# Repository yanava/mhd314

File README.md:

# Mahaudio MHD314 Audio DAC for the RaspberryPi

This is a hardware project for an open Hi-Fi DAC design for the RaspberryPi. MHD stands for Mahaudio Hi-Fi DAC and 314 is an obvious reference to the Pi. 

## Description

This is a project conducted through a series of YouTube live events, which can be accessed on the following playlist: https://www.youtube.com/watch?v=isWnR_Fm9iQ&list=PLo5SrSJMaUGJOzglfgmpuGIEasF4YtCA1&pp=iAQB - Portuguese language only for now. The purpose is educational, to show audio enthusiasts what is the necessary work to develop and integrate a product.

## Presentations

All presentations used on the live events are available under the Documentation folder. 

## License

This project is licensed under the BSD-3 License.

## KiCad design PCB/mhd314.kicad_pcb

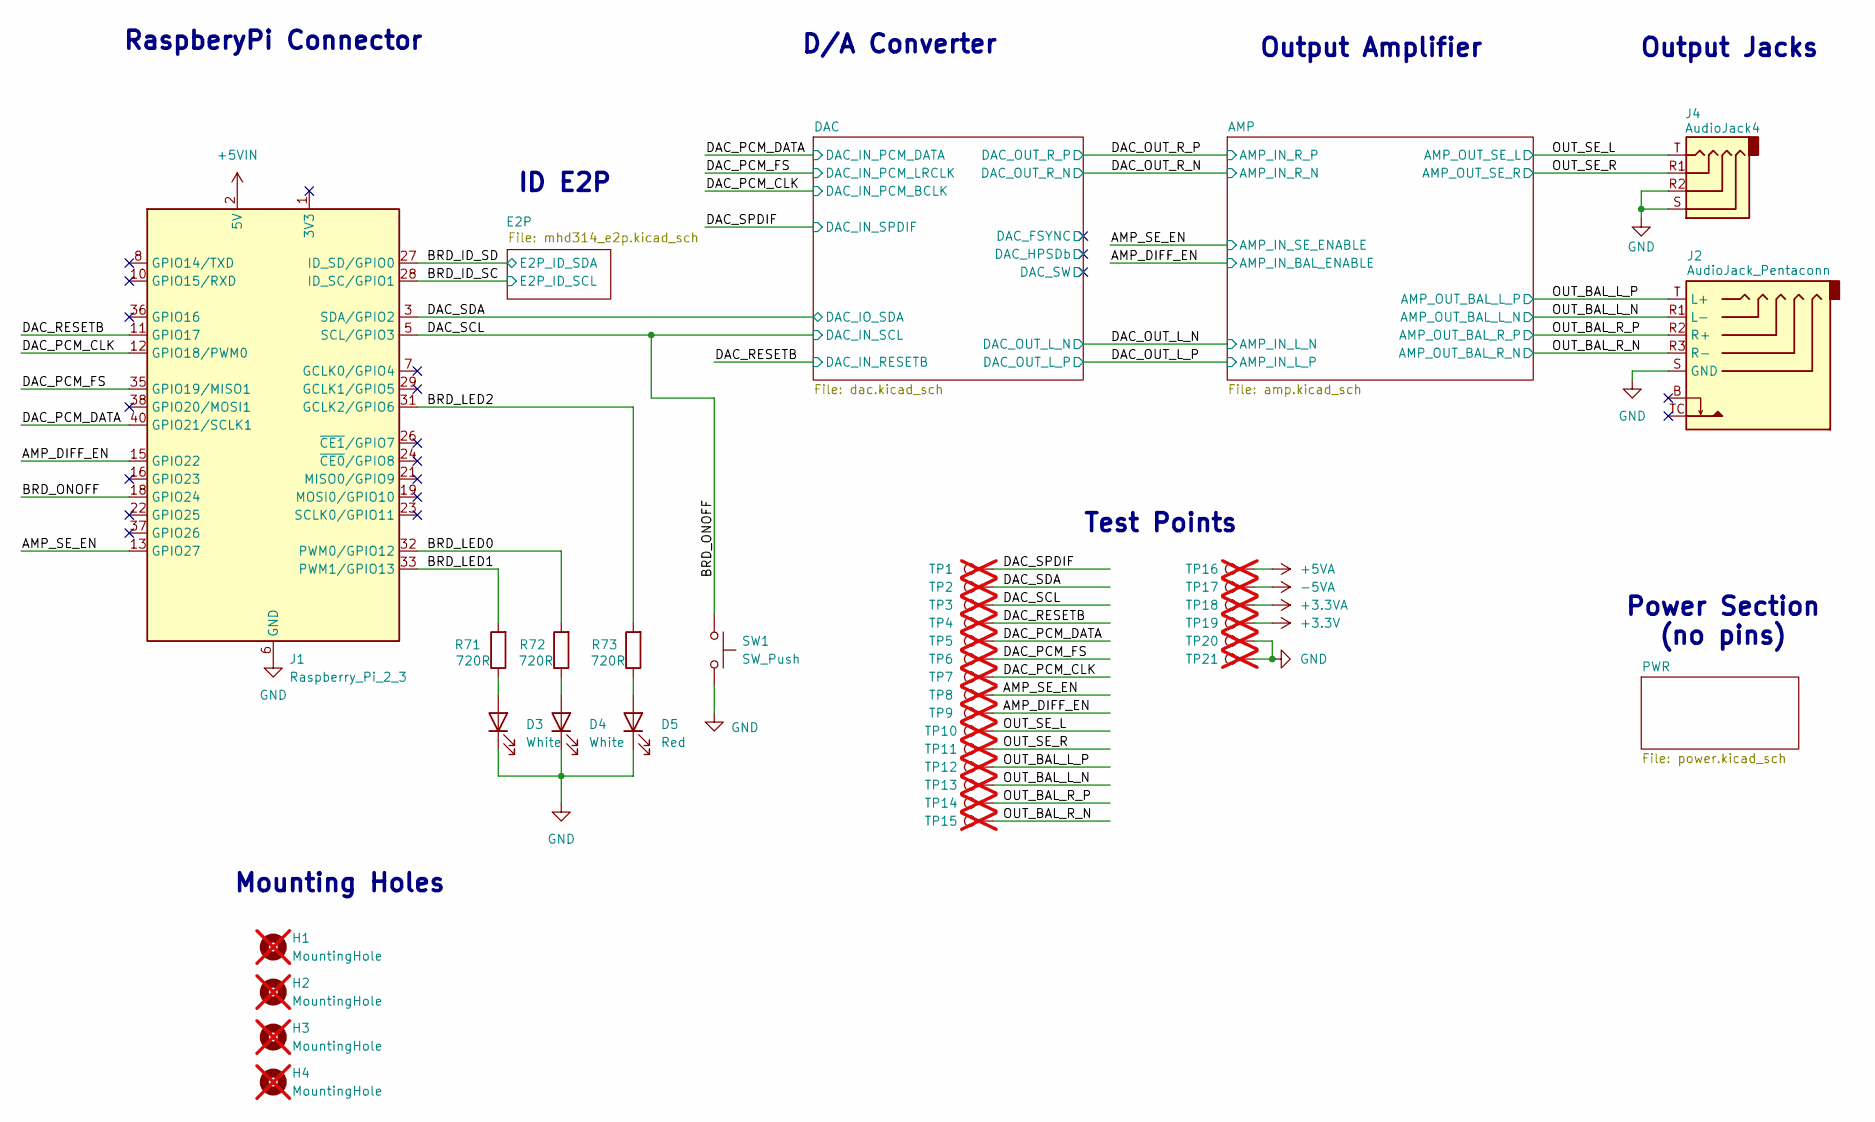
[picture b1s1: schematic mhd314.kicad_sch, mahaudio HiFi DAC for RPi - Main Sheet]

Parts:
D3, D4: White; LED_0603_1608Metric_Pad1.05x0.95mm_HandSolder; JLCPCB Part # C2290
D5: Red; LED_0603_1608Metric_Pad1.05x0.95mm_HandSolder; JLCPCB Part # C2286
H1, H2, H3, H4: MountingHole; MountingHole_2.7mm_M2.5_DIN965_Pad; not fitted
J1: Raspberry_Pi_2_3; PinSocket_2x20_P2.54mm_Vertical; JLCPCB Part # C132132
J2: AudioJack_Pentaconn; Jack_4.4mm_G-Switch_GT-3321667P-01_Horizontal; JLCPCB Part # C2762984
J4: AudioJack4; TENSILITY_54-00176; JLCPCB Part # C19857277
R71, R72, R73: 720R; R_0402_1005Metric_Pad0.72x0.64mm_HandSolder; Tolerance 1%; JLCPCB Part # C416571
SW1: SW_Push; SW_Tactile_SPST_Angled_PTS645Vx39-2LFS; JLCPCB Part # C285519
TP1, TP2, TP3, TP4, TP5, TP6, TP7, TP8, TP9, TP10, TP11, TP12, TP13, TP14, TP15, TP16, TP17, TP18, TP19, TP20, TP21: TestPoint; TestPoint_Pad_D1.0mm; not fitted

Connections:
+3.3V: TP19.1; also elsewhere on the board
+3.3VA: TP18.1; also elsewhere on the board
+5VA: TP16.1; also elsewhere on the board
+5VIN: J1.2 (5V), J1.4 (5V); also elsewhere on the board
-5VA: TP17.1; also elsewhere on the board
/AMP_DIFF_EN: J1.15 (GPIO22), TP9.1; also elsewhere on the board
/AMP_SE_EN: J1.13 (GPIO27), TP8.1; also elsewhere on the board
/BRD_ID_SC: J1.28 (ID_SC/GPIO1); also elsewhere on the board
/BRD_ID_SD: J1.27 (ID_SD/GPIO0); also elsewhere on the board
/BRD_LED0: J1.32 (PWM0/GPIO12), R72.2
/BRD_LED1: J1.33 (PWM1/GPIO13), R71.2
/BRD_LED2: J1.31 (GCLK2/GPIO6), R73.2
/BRD_ONOFF: J1.5 (SCL/GPIO3), J1.18 (GPIO24), SW1.1, TP3.1; also elsewhere on the board
/DAC_PCM_CLK: J1.12 (GPIO18/PWM0), TP7.1; also elsewhere on the board
/DAC_PCM_DATA: J1.40 (GPIO21/SCLK1), TP5.1; also elsewhere on the board
/DAC_PCM_FS: J1.35 (GPIO19/MISO1), TP6.1; also elsewhere on the board
/DAC_RESETB: J1.11 (GPIO17), TP4.1; also elsewhere on the board
/DAC_SDA: J1.3 (SDA/GPIO2), TP2.1; also elsewhere on the board
/DAC_SPDIF: TP1.1; also elsewhere on the board
/OUT_BAL_L_N: J2.R1 (L-), TP13.1; also elsewhere on the board
/OUT_BAL_L_P: J2.T (L+), TP12.1; also elsewhere on the board
/OUT_BAL_R_N: J2.R3 (R-), TP15.1; also elsewhere on the board
/OUT_BAL_R_P: J2.R2 (R+), TP14.1; also elsewhere on the board
/OUT_SE_L: J4.T, TP10.1; also elsewhere on the board
/OUT_SE_R: J4.R1, TP11.1; also elsewhere on the board
GND: D3.1 (K), D4.1 (K), D5.1 (K), J1.6 (GND), J1.9 (GND), J1.14 (GND), J1.20 (GND), J1.25 (GND), J1.30 (GND), J1.34 (GND), J1.39 (GND), J2.S (GND), J4.R2, J4.S, SW1.2, TP20.1, TP21.1; also elsewhere on the board
unnamed: D3.2 (A), R71.1
unnamed: D4.2 (A), R72.1
unnamed: D5.2 (A), R73.1

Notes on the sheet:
Test Points
Mounting Holes
Output Amplifier
ID E2P
Output Jacks
Power Section (no pins)
D/A Converter
RaspberyPi Connector

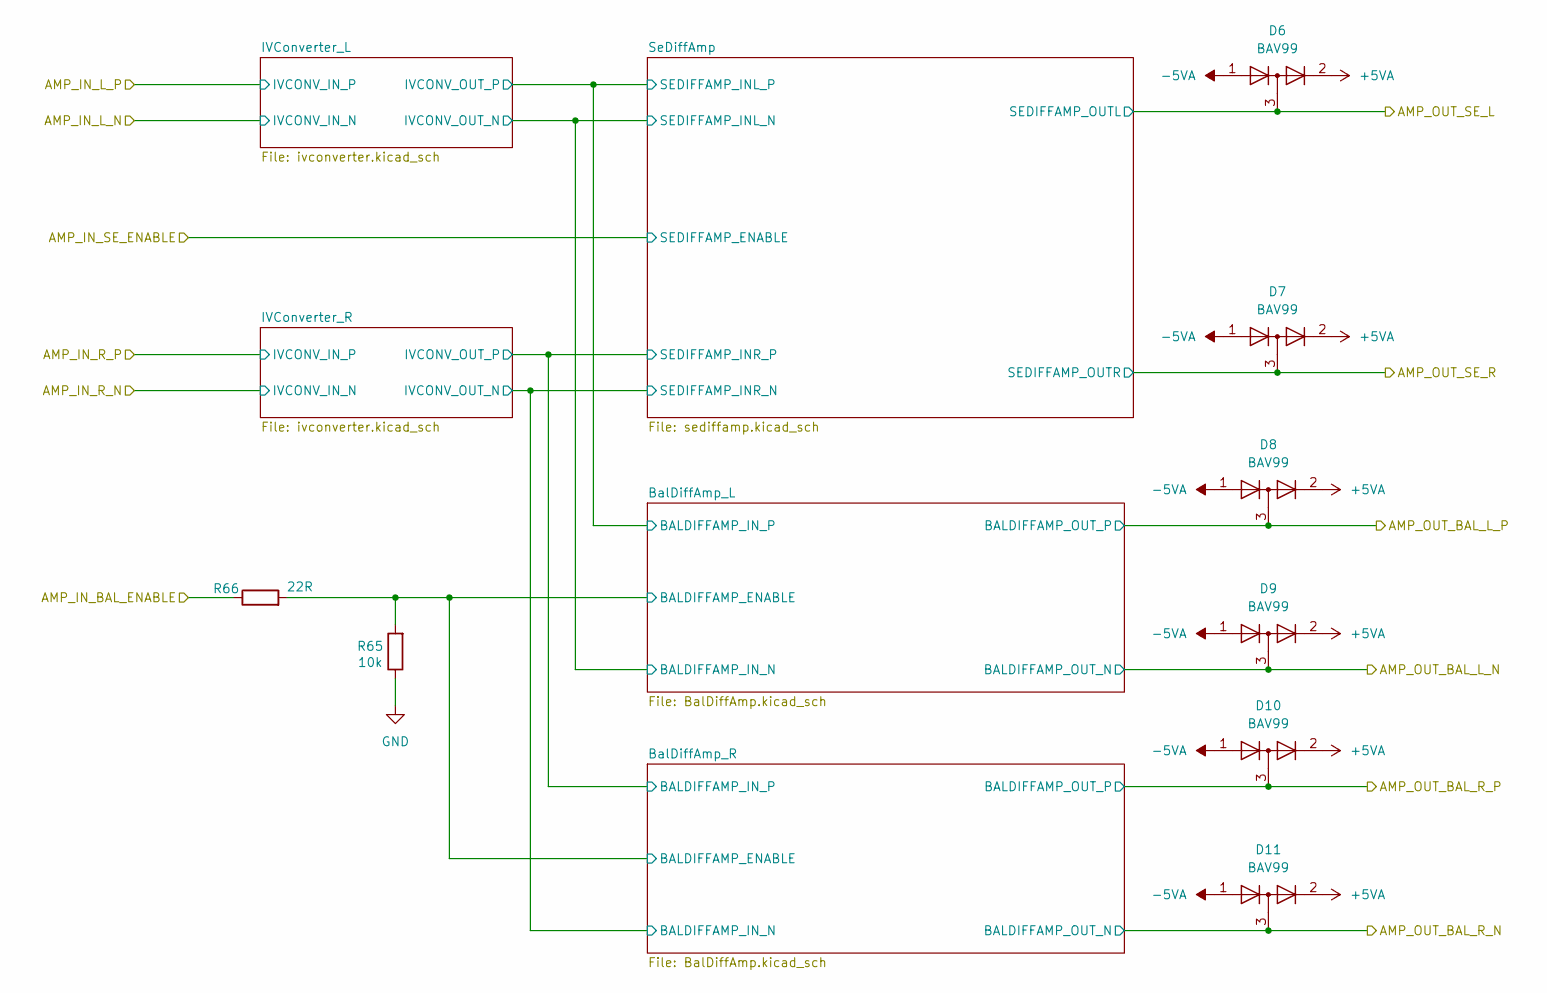
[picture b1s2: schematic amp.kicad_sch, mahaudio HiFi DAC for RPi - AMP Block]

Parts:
D6, D7, D8, D9, D10, D11: BAV99; SOT-23; JLCPCB Part # C2500
R65: 10k; R_0402_1005Metric_Pad0.72x0.64mm_HandSolder; Tolerance 5%; JLCPCB Part # C25744
R66: 22R; R_0402_1005Metric_Pad0.72x0.64mm_HandSolder; Tolerance 5%; JLCPCB Part # C25092

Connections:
+5VA: D6.2 (A), D7.2 (A), D8.2 (A), D9.2 (A), D10.2 (A), D11.2 (A); also elsewhere on the board
-5VA: D6.1 (K), D7.1 (K), D8.1 (K), D9.1 (K), D10.1 (K), D11.1 (K); also elsewhere on the board
/AMP/BalDiffAmp_L/BALDIFFAMP_ENABLE: R65.2, R66.2; also elsewhere on the board
/AMP_DIFF_EN: R66.1; also elsewhere on the board
/OUT_BAL_L_N: D9.3 (K); also elsewhere on the board
/OUT_BAL_L_P: D8.3 (K); also elsewhere on the board
/OUT_BAL_R_N: D11.3 (K); also elsewhere on the board
/OUT_BAL_R_P: D10.3 (K); also elsewhere on the board
/OUT_SE_L: D6.3 (K); also elsewhere on the board
/OUT_SE_R: D7.3 (K); also elsewhere on the board
GND: R65.1; also elsewhere on the board

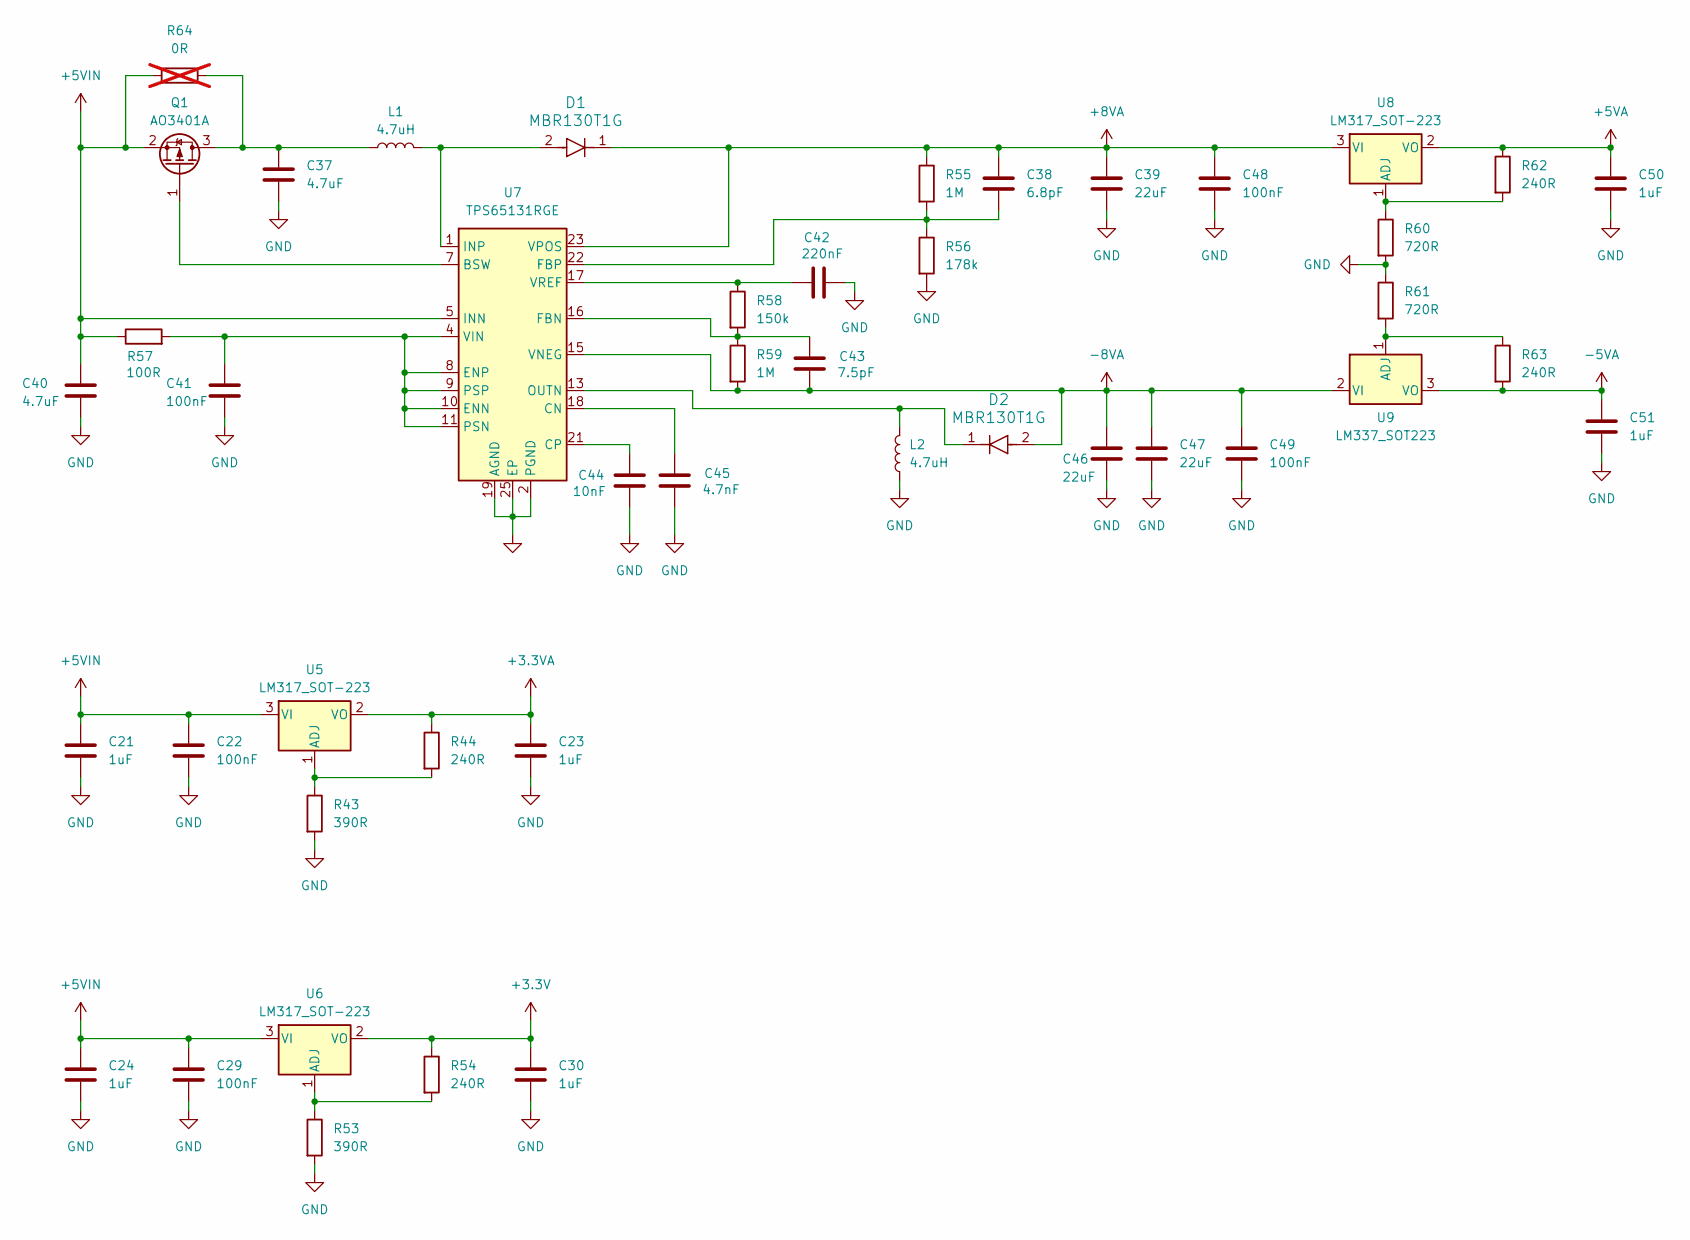
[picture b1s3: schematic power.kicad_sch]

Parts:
C21, C23, C24, C30, C50, C51: 1uF; C_0603_1608Metric_Pad1.08x0.95mm_HandSolder; Tolerance 10%; Voltage 16V; JLCPCB Part # C15849
C22, C29, C41, C48, C49: 100nF; C_0402_1005Metric_Pad0.74x0.62mm_HandSolder; Tolerance 10%; Voltage 16V; JLCPCB Part # C1525
C37: 4.7uF; C_0603_1608Metric_Pad1.08x0.95mm_HandSolder; Tolerance 10%; Voltage 10V; JLCPCB Part # C19666
C38: 6.8pF; C_0402_1005Metric_Pad0.74x0.62mm_HandSolder; Tolerance 0.1pF; Voltage 50V; JLCPCB Part # C88896
C39, C46, C47: 22uF; C_0603_1608Metric_Pad1.08x0.95mm_HandSolder; Tolerance 10%; Voltage 10V; JLCPCB Part # C84419
C40: 4.7uF; C_0603_1608Metric_Pad1.08x0.95mm_HandSolder; Voltage 10V; Tolerance 10%; JLCPCB Part # C19666
C42: 220nF; C_0402_1005Metric_Pad0.74x0.62mm_HandSolder; Tolerance 10%; Voltage 16V; JLCPCB Part # C16772
C43: 7.5pF; C_0402_1005Metric_Pad0.74x0.62mm_HandSolder; Tolerance 0.1pF; Voltage 50V; JLCPCB Part # C88938
C44: 10nF; C_0402_1005Metric_Pad0.74x0.62mm_HandSolder; Tolerance 10%; Voltage 50V; JLCPCB Part # C15195
C45: 4.7nF; C_0402_1005Metric_Pad0.74x0.62mm_HandSolder; Tolerance 10%; Voltage 50V; JLCPCB Part # C1538
D1, D2: MBR130T1G; SOD-123_425-04_ONS; JLCPCB Part # C82461
L1, L2: 4.7uH; WE-MAPI_4030; Tolerance 20%; Mfg Partnumber 74438357047; JLCPCB Part # C6707914
Q1: AO3401A; SOT-23; JLCPCB Part # C15127
R43, R53: 390R; R_0402_1005Metric_Pad0.72x0.64mm_HandSolder; Tolerance 1%; JLCPCB Part # C274891
R44, R54, R62, R63: 240R; R_0402_1005Metric_Pad0.72x0.64mm_HandSolder; Tolerance 1%; JLCPCB Part # C25094
R55, R59: 1M; R_0402_1005Metric_Pad0.72x0.64mm_HandSolder; Tolerance 1%; JLCPCB Part # C26083
R56: 178k; R_0402_1005Metric_Pad0.72x0.64mm_HandSolder; Tolerance 1%; JLCPCB Part # C185459
R57: 100R; R_0402_1005Metric_Pad0.72x0.64mm_HandSolder; Tolerance 5%; JLCPCB Part # C25076
R58: 150k; R_0402_1005Metric_Pad0.72x0.64mm_HandSolder; Tolerance 1%; JLCPCB Part # C25755
R60, R61: 720R; R_0402_1005Metric_Pad0.72x0.64mm_HandSolder; Tolerance 1%; JLCPCB Part # C416571
R64: 0R; R_0402_1005Metric_Pad0.72x0.64mm_HandSolder; not fitted
U5, U6, U8: LM317_SOT-223; SOT-223-3_TabPin2; JLCPCB Part # C84244
U7: TPS65131RGE; VQFN-24-1EP_4x4mm_P0.5mm_EP2.45x2.45mm_ThermalVias; JLCPCB Part # C87663
U9: LM337_SOT223; SOT-223-3_TabPin2; JLCPCB Part # C527400

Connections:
+3.3V: C30.1, R54.1, U6.2 (VO); also elsewhere on the board
+3.3VA: C23.1, R44.1, U5.2 (VO); also elsewhere on the board
+5VA: C50.1, R62.1, U8.2 (VO); also elsewhere on the board
+5VIN: C21.1, C22.1, C24.1, C29.1, C40.1, Q1.2 (S), R57.1, R64.1, U5.3 (VI), U6.3 (VI), U7.5 (INN), U7.6 (INN); also elsewhere on the board
+8VA: C38.1, C39.1, C48.1, D1.1, R55.1, U7.23 (VPOS), U8.3 (VI)
-5VA: C51.1, R63.2, U9.3 (VO); also elsewhere on the board
-8VA: C43.2, C46.1, C47.1, C49.1, D2.2, R59.2, U7.15 (VNEG), U9.2 (VI)
GND: C21.2, C22.2, C23.2, C24.2, C29.2, C30.2, C37.2, C39.2, C40.2, C41.2, C42.2, C44.2, C45.2, C46.2, C47.2, C48.2, C49.2, C50.2, C51.2, L2.1, R43.2, R53.2, R56.2, R60.2, R61.1, U7.2 (PGND), U7.3 (PGND), U7.19 (AGND), U7.25 (EP); also elsewhere on the board
unnamed: D1.2, L1.2, U7.1 (INP), U7.24 (INP)
unnamed: D2.1, L2.2, U7.13 (OUTN), U7.14 (OUTN)
unnamed: C37.1, L1.1, Q1.3 (D), R64.2
unnamed: Q1.1 (G), U7.7 (BSW)
unnamed: R43.1, R44.2, U5.1 (ADJ)
unnamed: R53.1, R54.2, U6.1 (ADJ)
unnamed: C45.1, U7.18 (CN)
unnamed: C44.1, U7.21 (CP)
unnamed: C41.1, R57.2, U7.4 (VIN), U7.8 (ENP), U7.9 (PSP), U7.10 (ENN), U7.11 (PSN)
unnamed: C43.1, R58.2, R59.1, U7.16 (FBN)
unnamed: C38.2, R55.2, R56.1, U7.22 (FBP)
unnamed: C42.1, R58.1, U7.17 (VREF)
unnamed: R60.1, R62.2, U8.1 (ADJ)
unnamed: R61.2, R63.1, U9.1 (ADJ)

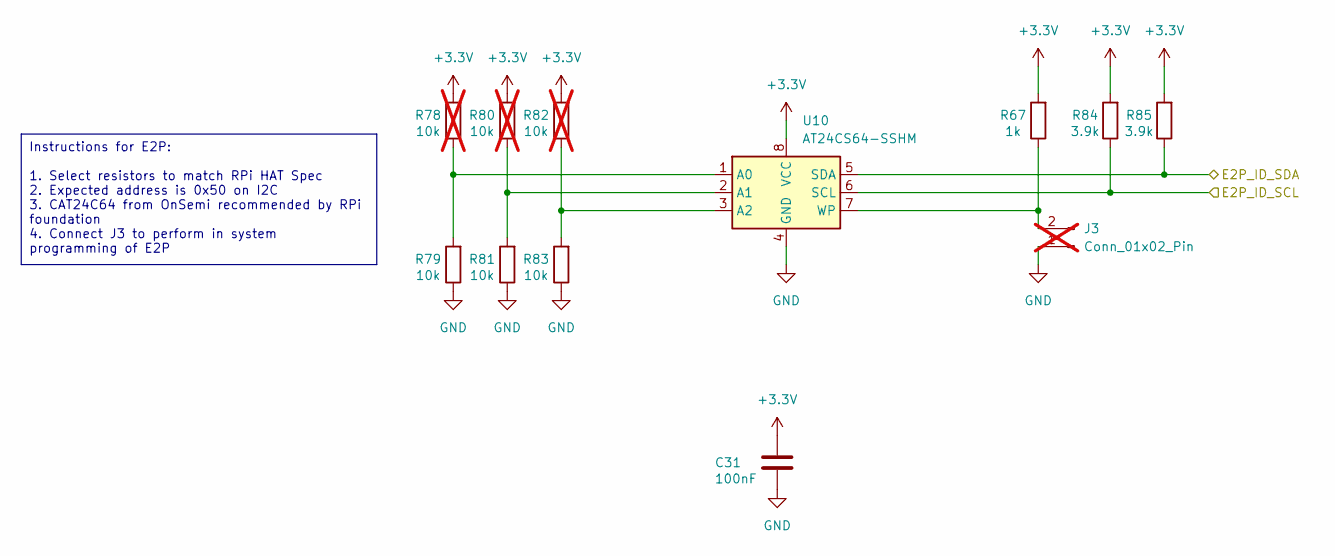
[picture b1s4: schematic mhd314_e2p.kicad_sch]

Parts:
C31: 100nF; C_0402_1005Metric_Pad0.74x0.62mm_HandSolder; Tolerance 10%; Voltage 16V; JLCPCB Part # C1525
J3: Conn_01x02_Pin; PinHeader_1x02_P1.00mm_Vertical; not fitted
R67: 1k; R_0402_1005Metric_Pad0.72x0.64mm_HandSolder; Tolerance 5%; JLCPCB Part # C11702
R78, R80, R82: 10k; R_0402_1005Metric_Pad0.72x0.64mm_HandSolder; Tolerance 5%; not fitted
R79, R81, R83: 10k; R_0402_1005Metric_Pad0.72x0.64mm_HandSolder; Tolerance 5%; JLCPCB Part # C25744
R84, R85: 3.9k; R_0402_1005Metric_Pad0.72x0.64mm_HandSolder; Tolerance 5%; JLCPCB Part # C51721
U10: AT24CS64-SSHM; SOIC-8_3.9x4.9mm_P1.27mm; JLCPCB Part # C81193

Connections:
+3.3V: C31.1, R67.2, R78.2, R80.2, R82.2, R84.2, R85.2, U10.8 (VCC); also elsewhere on the board
/BRD_ID_SC: R84.1, U10.6 (SCL); also elsewhere on the board
/BRD_ID_SD: R85.1, U10.5 (SDA); also elsewhere on the board
GND: C31.2, J3.1, R79.1, R81.1, R83.1, U10.4 (GND); also elsewhere on the board
unnamed: J3.2, R67.1, U10.7 (WP)
unnamed: R78.1, R79.2, U10.1 (A0)
unnamed: R80.1, R81.2, U10.2 (A1)
unnamed: R82.1, R83.2, U10.3 (A2)

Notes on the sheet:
Instructions for E2P: 1. Select resistors to match RPi HAT Spec 2. Expected address is 0x50 on I2C 3. CAT24C64 from OnSemi recommended by RPi foundation 4. Connect J3 to perform in system programming of E2P

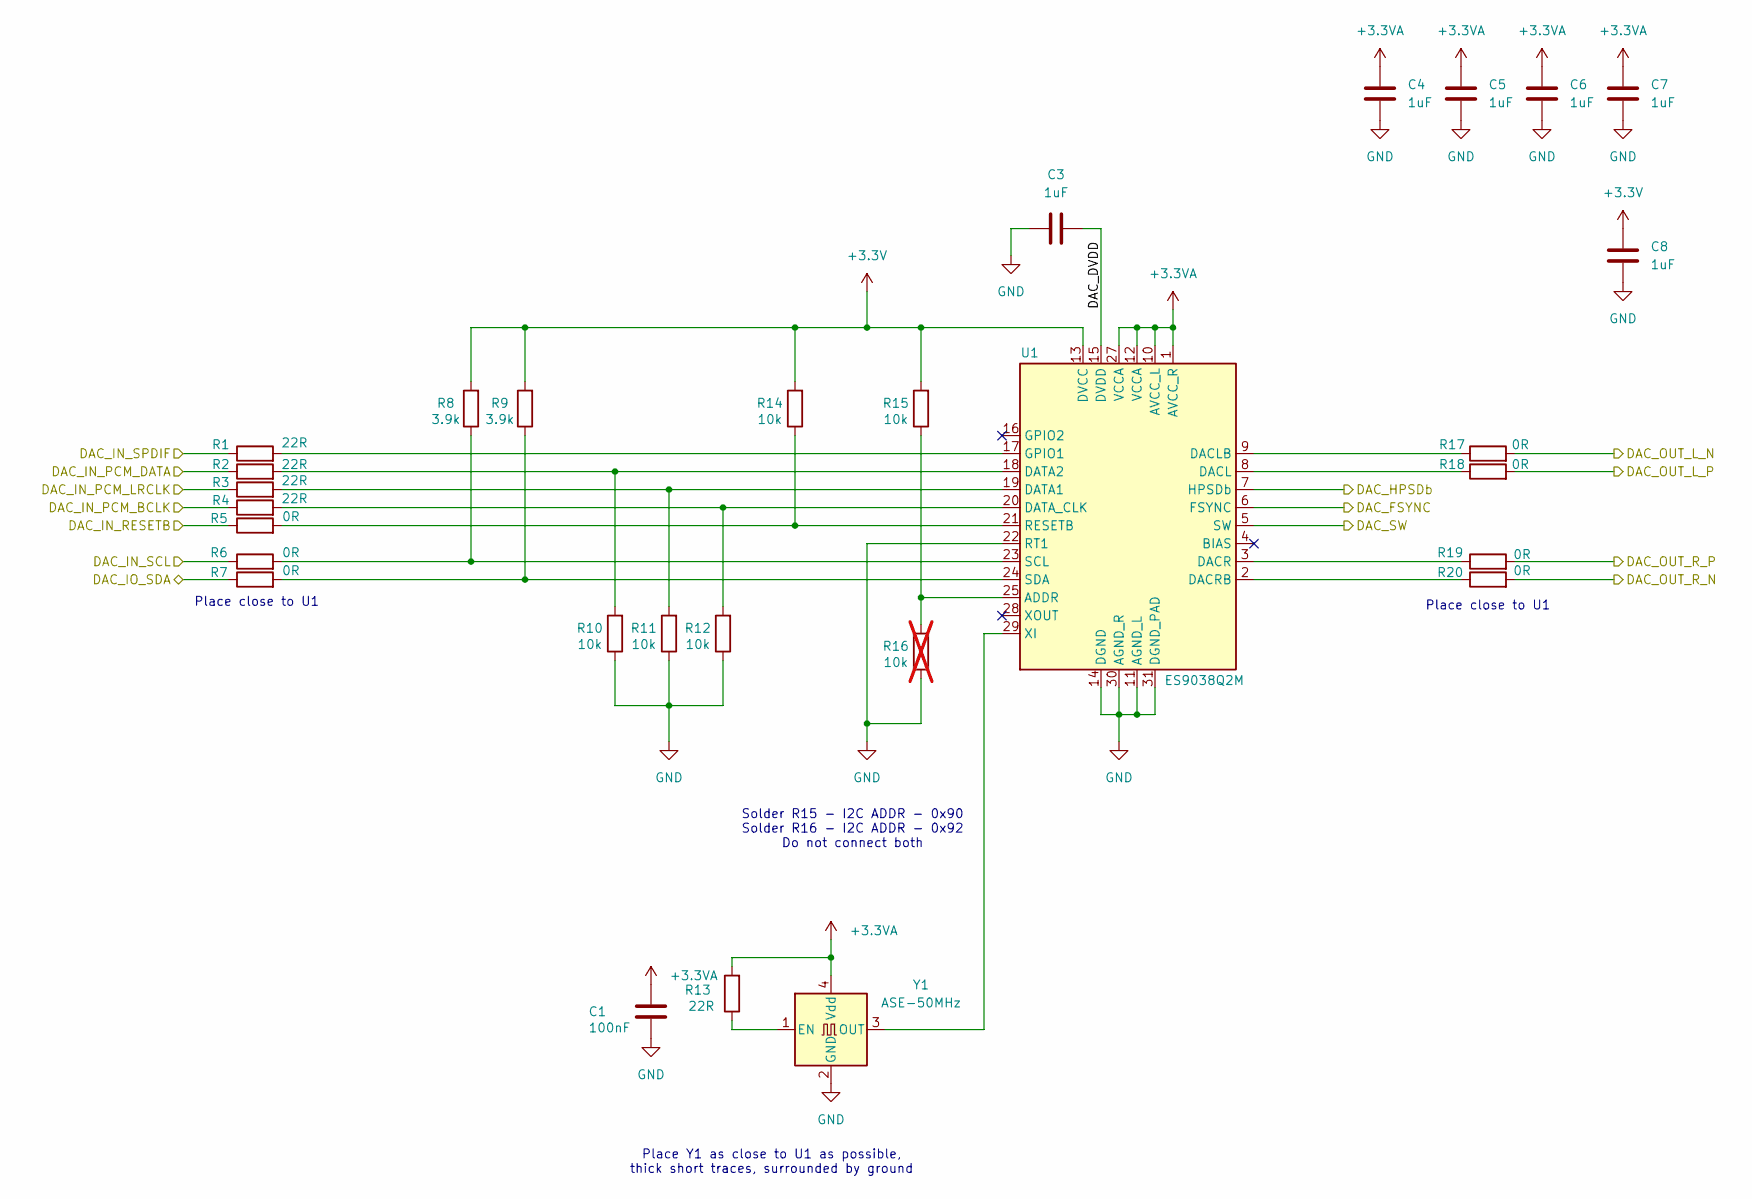
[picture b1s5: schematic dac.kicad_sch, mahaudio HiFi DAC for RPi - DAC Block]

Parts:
C1: 100nF; C_0402_1005Metric_Pad0.74x0.62mm_HandSolder; Tolerance 10%; Voltage 16V; JLCPCB Part # C1525
C3, C4, C5, C6, C7, C8: 1uF; C_0603_1608Metric_Pad1.08x0.95mm_HandSolder; Tolerance 10%; Voltage 16V; JLCPCB Part # C15849
R1, R2, R3, R4, R13: 22R; R_0402_1005Metric_Pad0.72x0.64mm_HandSolder; Tolerance 5%; JLCPCB Part # C25092
R5, R6, R7, R17, R18, R19, R20: 0R; R_0402_1005Metric_Pad0.72x0.64mm_HandSolder; JLCPCB Part # C17168
R8, R9: 3.9k; R_0402_1005Metric_Pad0.72x0.64mm_HandSolder; Tolerance 5%; JLCPCB Part # C51721
R10, R11, R12, R14, R15: 10k; R_0402_1005Metric_Pad0.72x0.64mm_HandSolder; Tolerance 5%; JLCPCB Part # C25744
R16: 10k; R_0402_1005Metric_Pad0.72x0.64mm_HandSolder; Tolerance 5%; not fitted
U1: ES9038Q2M; QFN-30_EP_3x5_Pitch0.4mm; JLCPCB Part # C2682306
Y1: ASE-50MHz; Oscillator_SMD_Abracon_ASE-4Pin_3.2x2.5mm; JLCPCB Part # C19725350

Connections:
+3.3V: C8.1, R8.2, R9.2, R14.2, R15.2, U1.13 (DVCC); also elsewhere on the board
+3.3VA: C1.1, C4.1, C5.1, C6.1, C7.1, R13.2, U1.1 (AVCC_R), U1.10 (AVCC_L), U1.12 (VCCA), U1.27 (VCCA), Y1.4 (Vdd); also elsewhere on the board
/BRD_ONOFF: R6.1; also elsewhere on the board
/DAC/DAC_DVDD: C3.2, U1.15 (DVDD)
/DAC/DAC_FSYNC: U1.6 (FSYNC)
/DAC/DAC_HPSDb: U1.7 (HPSDb)
/DAC/DAC_SW: U1.5 (SW)
/DAC_OUT_L_N: R17.2; also elsewhere on the board
/DAC_OUT_L_P: R18.2; also elsewhere on the board
/DAC_OUT_R_N: R20.2; also elsewhere on the board
/DAC_OUT_R_P: R19.2; also elsewhere on the board
/DAC_PCM_CLK: R4.1; also elsewhere on the board
/DAC_PCM_DATA: R2.1; also elsewhere on the board
/DAC_PCM_FS: R3.1; also elsewhere on the board
/DAC_RESETB: R5.1; also elsewhere on the board
/DAC_SDA: R7.1; also elsewhere on the board
/DAC_SPDIF: R1.1; also elsewhere on the board
GND: C1.2, C3.1, C4.2, C5.2, C6.2, C7.2, C8.2, R10.1, R11.1, R12.1, R16.1, U1.11 (AGND_L), U1.14 (DGND), U1.22 (RT1), U1.30 (AGND_R), U1.31 (DGND_PAD), Y1.2 (GND); also elsewhere on the board
unnamed: R15.1, R16.2, U1.25 (ADDR)
unnamed: R18.1, U1.8 (DACL)
unnamed: R17.1, U1.9 (DACLB)
unnamed: R19.1, U1.3 (DACR)
unnamed: R20.1, U1.2 (DACRB)
unnamed: R3.2, R11.2, U1.19 (DATA1)
unnamed: R2.2, R10.2, U1.18 (DATA2)
unnamed: R4.2, R12.2, U1.20 (DATA_CLK)
unnamed: R1.2, U1.17 (GPIO1)
unnamed: R5.2, R14.1, U1.21 (RESETB)
unnamed: R6.2, R8.1, U1.23 (SCL)
unnamed: R7.2, R9.1, U1.24 (SDA)
unnamed: U1.29 (XI), Y1.3 (OUT)
unnamed: R13.1, Y1.1 (EN)

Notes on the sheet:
Place close to U1
Solder R15 - I2C ADDR - 0x90 Solder R16 - I2C ADDR - 0x92 Do not connect both
Place Y1 as close to U1 as possible, thick short traces, surrounded by ground

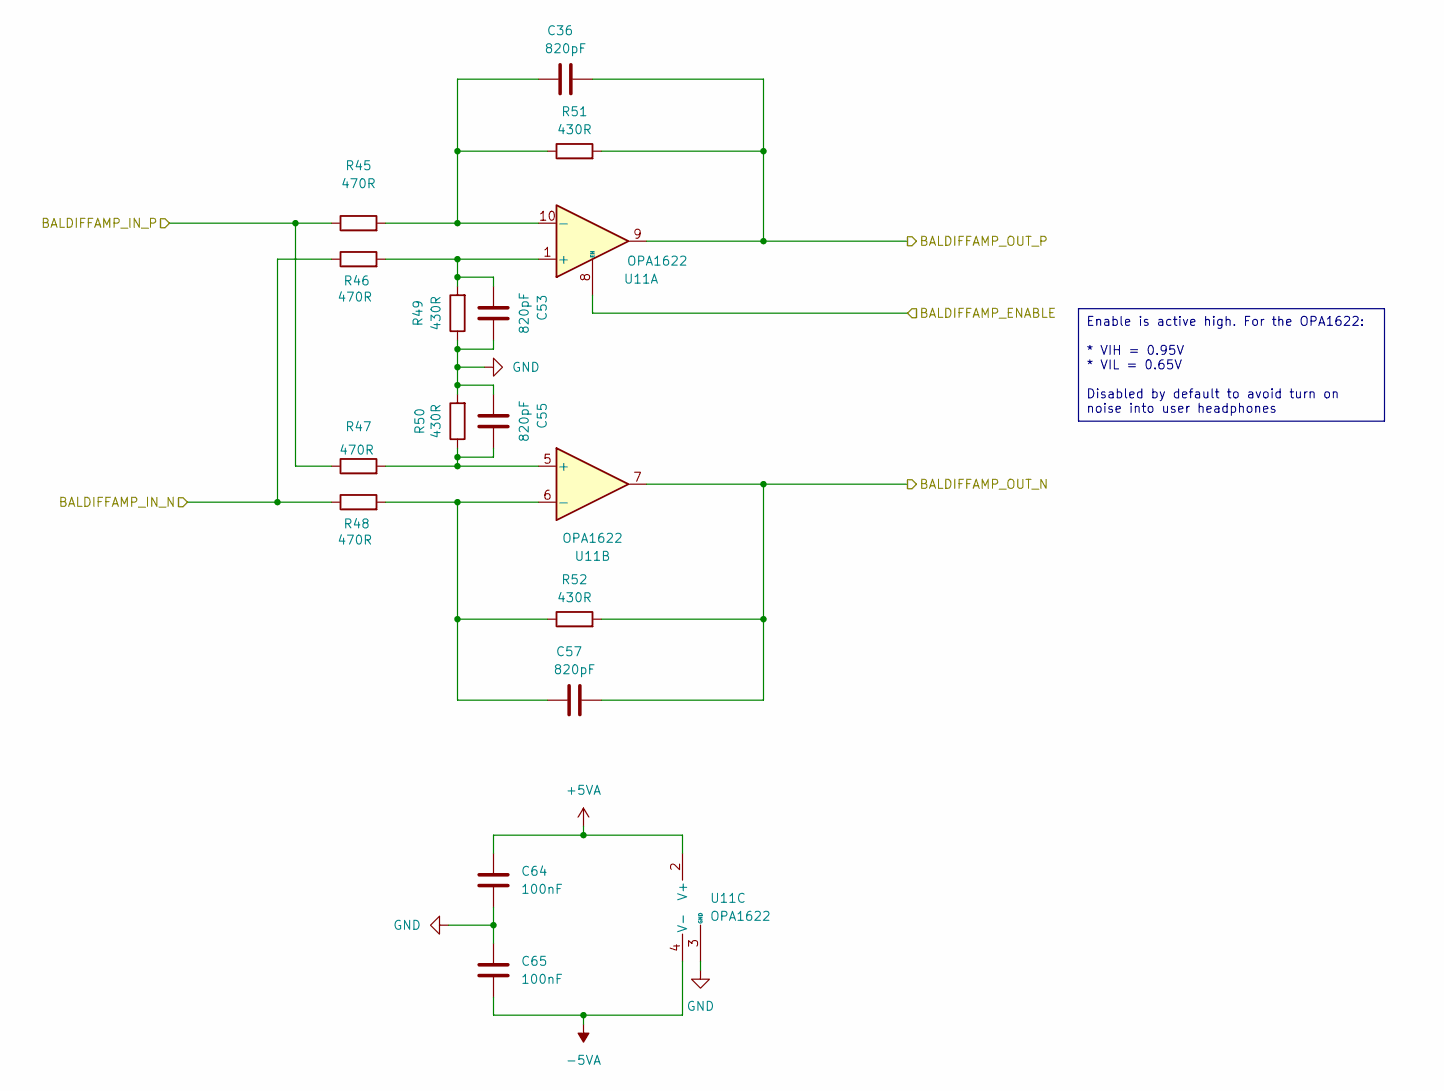
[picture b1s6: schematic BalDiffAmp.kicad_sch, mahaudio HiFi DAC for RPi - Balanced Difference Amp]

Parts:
C36, C53, C55, C57: 820pF; C_0603_1608Metric_Pad1.08x0.95mm_HandSolder; Tolerance 10%; Voltage 50V; JLCPCB Part # C99081
C64, C65: 100nF; C_0402_1005Metric_Pad0.74x0.62mm_HandSolder; Tolerance 10%; Voltage 16V; JLCPCB Part # C1525
R45, R46, R47, R48: 470R; R_0402_1005Metric_Pad0.72x0.64mm_HandSolder; Tolerance 0.1%; JLCPCB Part # C445590
R49, R50, R51, R52: 430R; R_0402_1005Metric_Pad0.72x0.64mm_HandSolder; Tolerance 0.1%; JLCPCB Part # C186317
U11: OPA1622; Texas_S-PVSON-N10; JLCPCB Part # C2876559

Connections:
+5VA: C64.1, U11.2 (V+); also elsewhere on the board
-5VA: C65.2, U11.4 (V-), U11.11 (V-); also elsewhere on the board
/AMP/BalDiffAmp_L/BALDIFFAMP_ENABLE: U11.8 (EN); also elsewhere on the board
/AMP/BalDiffAmp_L/BALDIFFAMP_IN_N: R46.1, R48.1; also elsewhere on the board
/AMP/BalDiffAmp_L/BALDIFFAMP_IN_P: R45.1, R47.1; also elsewhere on the board
/OUT_BAL_L_N: C57.2, R52.2, U11.7; also elsewhere on the board
/OUT_BAL_L_P: C36.2, R51.2, U11.9; also elsewhere on the board
GND: C53.2, C55.1, C64.2, C65.1, R49.1, R50.2, U11.3 (GND); also elsewhere on the board
unnamed: C53.1, R46.2, R49.2, U11.1 (+)
unnamed: C36.1, R45.2, R51.1, U11.10 (-)
unnamed: C55.2, R47.2, R50.1, U11.5 (+)
unnamed: C57.1, R48.2, R52.1, U11.6 (-)

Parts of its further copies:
C35, C52, C54, C56: 820pF; C_0603_1608Metric_Pad1.08x0.95mm_HandSolder; Tolerance 10%; Voltage 50V; JLCPCB Part # C99081
C60, C61: 100nF; C_0402_1005Metric_Pad0.74x0.62mm_HandSolder; Tolerance 10%; Voltage 16V; JLCPCB Part # C1525
R35, R36, R39, R40: 470R; R_0402_1005Metric_Pad0.72x0.64mm_HandSolder; Tolerance 0.1%; JLCPCB Part # C445590
R37, R38, R41, R42: 430R; R_0402_1005Metric_Pad0.72x0.64mm_HandSolder; Tolerance 0.1%; JLCPCB Part # C186317
U4: OPA1622; Texas_S-PVSON-N10; JLCPCB Part # C2876559

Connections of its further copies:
+5VA: C60.1, U4.2 (V+); also elsewhere on the board
-5VA: C61.2, U4.4 (V-), U4.11 (V-); also elsewhere on the board
/AMP/BalDiffAmp_L/BALDIFFAMP_ENABLE: U4.8 (EN); also elsewhere on the board
/AMP/BalDiffAmp_R/BALDIFFAMP_IN_N: R36.1, R40.1; also elsewhere on the board
/AMP/BalDiffAmp_R/BALDIFFAMP_IN_P: R35.1, R39.1; also elsewhere on the board
/OUT_BAL_R_N: C56.2, R42.2, U4.7; also elsewhere on the board
/OUT_BAL_R_P: C35.2, R37.2, U4.9; also elsewhere on the board
GND: C52.2, C54.1, C60.2, C61.1, R38.1, R41.2, U4.3 (GND); also elsewhere on the board
unnamed: C52.1, R36.2, R38.2, U4.1 (+)
unnamed: C35.1, R35.2, R37.1, U4.10 (-)
unnamed: C54.2, R39.2, R41.1, U4.5 (+)
unnamed: C56.1, R40.2, R42.1, U4.6 (-)

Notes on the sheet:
Enable is active high. For the OPA1622: * VIH = 0.95V * VIL = 0.65V Disabled by default to avoid turn on noise into user headphones

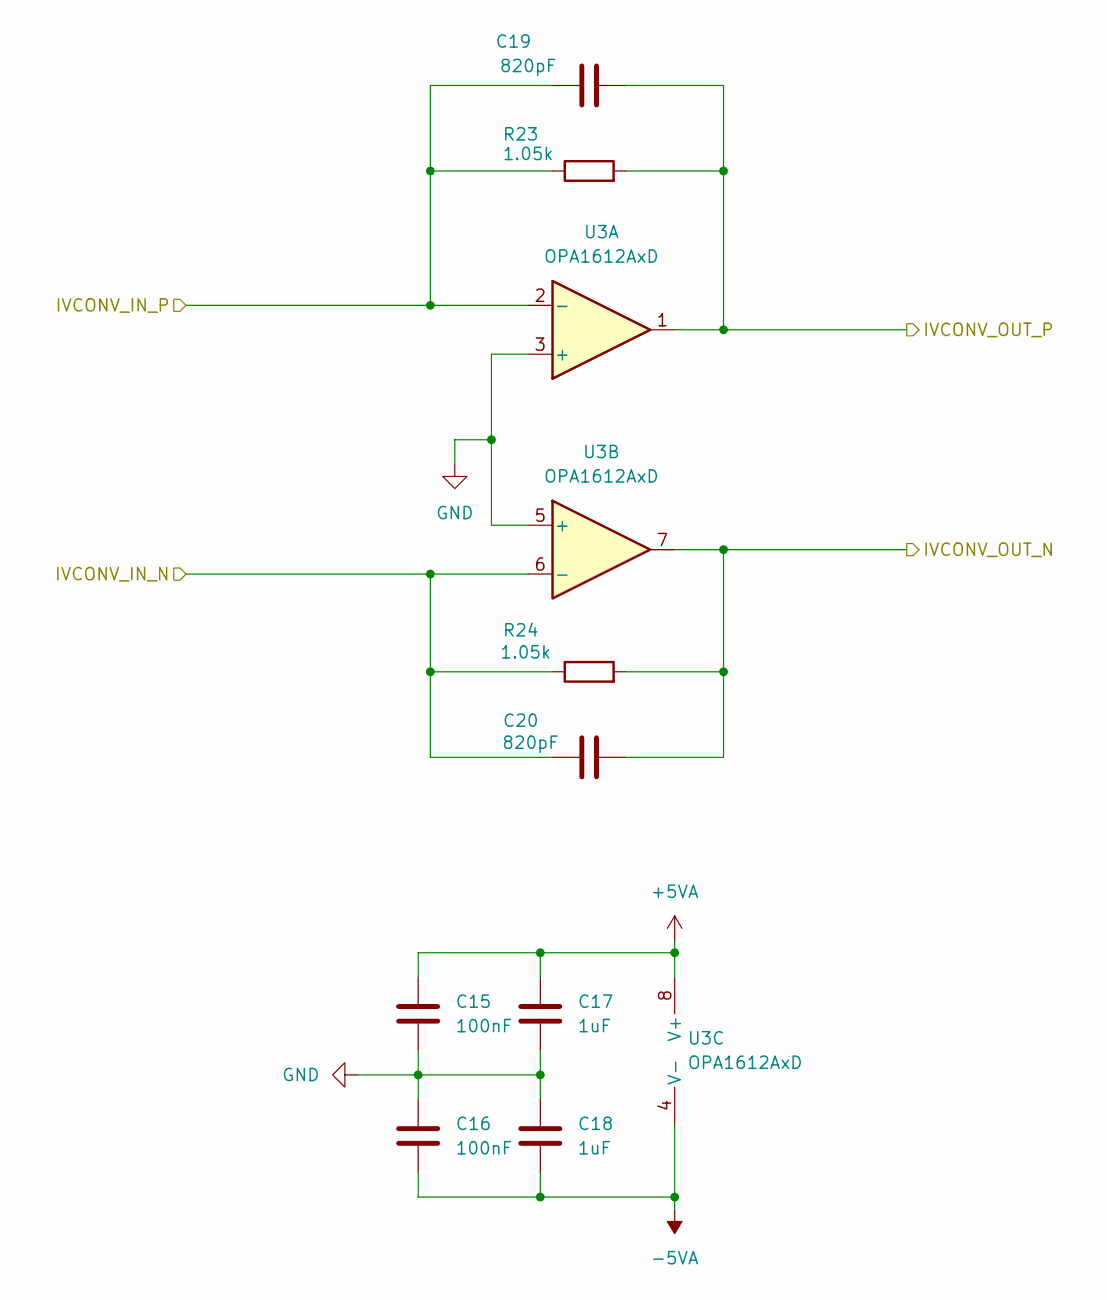
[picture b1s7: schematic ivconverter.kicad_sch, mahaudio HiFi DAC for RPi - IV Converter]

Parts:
C15, C16: 100nF; C_0402_1005Metric_Pad0.74x0.62mm_HandSolder; Tolerance 10%; Voltage 16V; JLCPCB Part # C1525
C17, C18: 1uF; C_0603_1608Metric_Pad1.08x0.95mm_HandSolder; Tolerance 10%; Voltage 16V; JLCPCB Part # C15849
C19, C20: 820pF; C_0603_1608Metric_Pad1.08x0.95mm_HandSolder; Tolerance 10%; Voltage 50V; JLCPCB Part # C99081
R23, R24: 1.05k; R_0402_1005Metric_Pad0.72x0.64mm_HandSolder; Tolerance 0.1%; JLCPCB Part # C2693047
U3: OPA1612AxD; SOIC-8_3.9x4.9mm_P1.27mm; JLCPCB Part # C94590

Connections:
+5VA: C15.1, C17.1, U3.8 (V+); also elsewhere on the board
-5VA: C16.2, C18.2, U3.4 (V-); also elsewhere on the board
/AMP/BalDiffAmp_R/BALDIFFAMP_IN_N: C20.2, R24.2, U3.7; also elsewhere on the board
/AMP/BalDiffAmp_R/BALDIFFAMP_IN_P: C19.2, R23.2, U3.1; also elsewhere on the board
/DAC_OUT_R_N: C20.1, R24.1, U3.6 (-); also elsewhere on the board
/DAC_OUT_R_P: C19.1, R23.1, U3.2 (-); also elsewhere on the board
GND: C15.2, C16.1, C17.2, C18.1, U3.3 (+), U3.5 (+); also elsewhere on the board

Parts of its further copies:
C9, C10: 100nF; C_0402_1005Metric_Pad0.74x0.62mm_HandSolder; Tolerance 10%; Voltage 16V; JLCPCB Part # C1525
C11, C12: 1uF; C_0603_1608Metric_Pad1.08x0.95mm_HandSolder; Tolerance 10%; Voltage 16V; JLCPCB Part # C15849
C13, C14: 820pF; C_0603_1608Metric_Pad1.08x0.95mm_HandSolder; Tolerance 10%; Voltage 50V; JLCPCB Part # C99081
R21, R22: 1.05k; R_0402_1005Metric_Pad0.72x0.64mm_HandSolder; Tolerance 0.1%; JLCPCB Part # C2693047
U2: OPA1612AxD; SOIC-8_3.9x4.9mm_P1.27mm; JLCPCB Part # C94590

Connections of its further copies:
+5VA: C9.1, C11.1, U2.8 (V+); also elsewhere on the board
-5VA: C10.2, C12.2, U2.4 (V-); also elsewhere on the board
/AMP/BalDiffAmp_L/BALDIFFAMP_IN_N: C14.2, R22.2, U2.7; also elsewhere on the board
/AMP/BalDiffAmp_L/BALDIFFAMP_IN_P: C13.2, R21.2, U2.1; also elsewhere on the board
/DAC_OUT_L_N: C14.1, R22.1, U2.6 (-); also elsewhere on the board
/DAC_OUT_L_P: C13.1, R21.1, U2.2 (-); also elsewhere on the board
GND: C9.2, C10.1, C11.2, C12.1, U2.3 (+), U2.5 (+); also elsewhere on the board
